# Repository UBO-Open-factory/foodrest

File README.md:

> **Attention**
> Ce projet est en cours de développement.

# FoodRest
Code pour le Projet de poubelle connectée basée sur la solution Open Source [TOCIO](https://github.com/UBO-Open-factory/TOCIO-Back-office) permettant de collecter et afficher des données.

Ce projet présente le code Arduino pour un ESP32.

# Principe de fonctionnement du programme
Principe d’enregistrement de mesures lors de l’utilisation de la poubelle connectée.

En jaune : Les interactions avec l’utilisateur.
En Rouge, ce qu'il faut encore affiner.

# Installations
## Librairies Arduino utilisées
Plusieures librairies tierces sont utilisées dans le projet, pour faciliter l'intégration elles sont toutes mises 
dans le répertoire **Librairies**. 
Il suffi donc de les prendre et de les glisser dans le répertoire Arduino/librairies 
(Sous windows : C:\Users\<user>\Documents\Arduino\libraries en remplacant <user> par votre nom d'utilisateur windows.

### SDConfigFile
La librairie **SDConfigFile** est la librairie disponible sur le [dépot Git](https://github.com/bneedhamia/sdconfigfile)

Cette librairie est également disponible dans le répertoire du projet (répertoire /Librairies/SDConfigFile ).

### WiFiClientSecure
La librairie **WiFiClientSecure** est la librairie disponible sur le [dépot Git](https://github.com/espressif/arduino-esp32/tree/master/libraries/WiFiClientSecure)

Cette librairie est également disponible dans le répertoire du projet (répertoire /Librairies/WiFiClientSecure ).

### RTC
La librairie **RTC** utilisée est celle disponible sur le [dépot Git officiel Adafruit](https://github.com/adafruit/RTClib)
[Mode d'emploi](https://learn.adafruit.com/adafruit-pcf8523-real-time-clock?view=all)

Cette librairie est également disponible dans le répertoire du projet (répertoire /Librairies/RTClib ).

### Balance (HX711)
La librairie **HX711** utilisée est celle disponible sur le [dépot GIT](https://github.com/bogde/HX711)

Cette librairie est également disponible dans le répertoire du projet (répertoire /Librairies/HX711 ).

## Dépendance des librairies utilisées
Les librairies doivent être incluses les unes par rapport au autres dans l'ordre suivant :
* globalVariable.h
  * SPI.h
* GestionErreur.h
* Config.h
  * SDCard.h
	* SDConfigFile.h
		* SD.h
	* FS.h
	* SPI.h
* Tocio.h
  * WiFiClientSecure.h
    * WiFi.h
* Balance.h
  * HX711.h
* RTC.h
  * Wire.h
  * RTClib.h
  * NTPClient.h
  * WiFiUDP.h
* IDpoubelle.h
* Functions.h
  * Wire.h

# Configuration de Arduino
## Installation des cartes ESP32 dans l'IDe Arduino
Lancez l’IDE Arduino et ouvrez les préférences depuis le menu Fichier. Sur macOS, allez dans le menu Arduino puis Préférences… Cliquez sur l’icône indiquée par la flèche rouge sur la photo ci-dessous.

Dans le champ de saisie, collez l’adresse internet suivante puis validez
```
https://dl.espressif.com/dl/package_esp32_index.json
```
> Si vous avez déjà des définitions de cartes, vous pouvez les cumuler en les les séparant par des virgules.
> Par exemple, dans mon cas j'ai : http://arduino.esp8266.com/stable/package_esp8266com_index.json,https://dl.espressif.com/dl/package_esp32_index.json

Maintenant, allez dans le menu Outils > Type de Cartes > Gestionnaire de carte.
Dans le champ de recherche, saisissez ESP32 pour trouver les nouvelles cartes à installer. Si les cartes n’apparaissent pas, vérifiez dans les préférences que l’URL est correcte. vérifiez également la connexion Internet. Cliquer sur Installer

L’installation terminée, fermez le gestionnaire de carte et ouvrez de nouveau le menu Outils > Type de Carte. 
Vous avez maintenant une nouvelle section appelée ESP32 Boards (2.7.4)

## Sélection de la carte

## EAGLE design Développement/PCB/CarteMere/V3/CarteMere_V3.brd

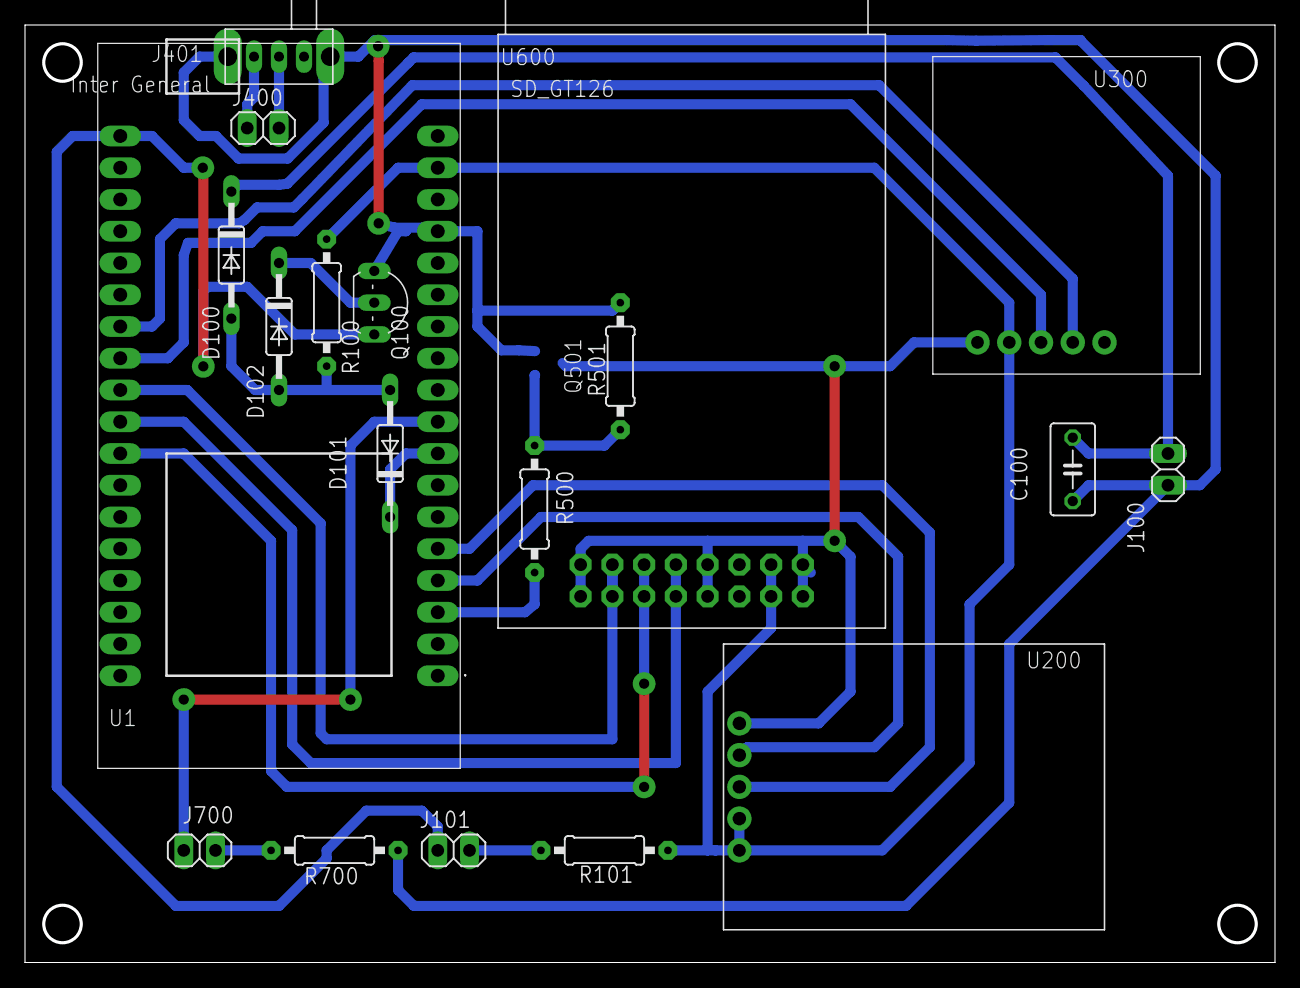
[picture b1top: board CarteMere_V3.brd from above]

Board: 2 copper layers, 99.7 x 74.7 mm, 20 parts (1 on the bottom side), 22 nets.

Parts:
C100: 10n; C050-035X075
D100, D101, D102: 1N4148; DO35-10
J100: Capteur ILS; 1X02
J101: LED_CAPOT; 1X02
J400: Inter batterie; 1X02
J401: Inter General; COMMUTATEUR_GLISSIERE_1RT_100MA
J700: LED_PESEE; 1X02
Q100: 2N5551; TO92-EBC
Q501: SI2302DS; SOT23
R100: 100k; 0207/10
R101: 470R; 0207/10
R500, R700: 100R; 0207/10
R501: 1M; 0207/10
U1: FIREBEETLE-ESP32-DFR0478; FIREBEETLE_ESP32
U200: HX711; SPARKFUN_HX711_LOAD_CELL
U300: RTC_ADA-3295; ADA3295
U600: SD_GT126

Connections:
3V3: R100.2, R101.2, U1.17, U200.VCC, U200.VDD, U300.2, U600.3V3@6, U600.3V3@9
GND: C100.2, J100.1, J401.GNDA, J401.GNDB, Q100.E, Q501.2, R501.1, R700.1, U1.15
GND_C: Q501.3, U200.GND, U300.1, U600.CS@4, U600.CS@11, U600.GND@0, U600.GND@7, U600.GND@8, U600.GND@15
GND_C_EN: R500.1, U1.3
HX711_CLK: U1.4, U200.CLK
HX711_DAT: U1.5, U200.DAT
I2C_SCL: U1.30, U300.4
I2C_SDA: U1.29, U300.3
LED_CAPOT_PLUS: J101.1, R101.1
LED_PESEE: J700.1, U1.9
MASQUE_RESET_EN: D101.C, U1.8
unnamed: Q501.1, R500.2, R501.2
unnamed: J700.2, R700.2
unnamed: D100.A, D101.A, D102.A, R100.1
unnamed: C100.1, D100.C, J100.2
unnamed: D102.C, Q100.B
unnamed: J400.2, J401.COM
unnamed: J400.1, J401.OUTA
RESET: J101.2, Q100.C, U1.36
SPI_MISO: U1.28, U600.MISO@1, U600.MISO@14
SPI_MOSI: U1.27, U600.MOSI@3, U600.MOSI@12
SPI_SCK: U1.26, U600.SCK@2, U600.SCK@13

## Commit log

2021-03-08 Librairie Arduino
2021-03-08 verssion test non_fontionnel
2021-03-08 integration lib wificlient secure
2021-03-08 suppression de variable
    !attention fonction :sendDataInHTTPSRequest(String data)
    non fonctionnel
2021-03-08 Initialisation du wifi
2021-03-08 Nettoyage du code
2021-03-09 Séparation du code en librairies
2021-03-09 Factorisation du code dans les fichiers de fonctions
2021-03-09 complément fonction + ajout fonction + commentary
    - ajout du pin maping des indicateur visuel + capteur CZL635_20
    - complement fonction CZL635_20 capteur de poid
    - complement fonction RTC en cours
    - ajout lien preference carte firebeetle esp8266
2021-03-09 complément fonction RTC "pcf8523"
2021-03-09 suppression bout de code RTC inutile + procedure de test
2021-03-09 Mise en place de la structure du main
2021-03-09 ajout lib capteur poid, nom lib "HX711"
2021-03-10 Utilisation du fichier de paramétrage pour la calibration
2021-03-10 Nettoyage de code et commentaires
2021-03-10 Suppression code innutil
2021-03-10 librairie RTC
2021-03-10 Correction erreur de typo
2021-03-10 Lecture de la configuration à partir de la (fake) carte SD
    Pour l'instant on utilise une fonction avec les paramètres écrit en dur
2021-03-10 Algorythme d'envoie des mesures.
2021-03-10 La fonction RTC doit renvoyer une string
2021-03-10 Documentation des librairies utilisées
2021-03-12 Modification de l'URL pour le BO de TOCIO
    On utilise maintenant le BO spécifique au projet Food Rest
2021-03-12 wificlient sercure non compatible firebeetle
2021-03-12 correction connection wifi version 2016
2021-03-12 space
2021-03-12 tentative de deggu
    pb au niveau de fonction -> niveau_battrie
    apres le "debug f2"
2021-03-12 Création d'un fichier de configuration type
    Ce fichier sera à mettre sur la carte SD
2021-03-12 Mise en place du calibrage usine
2021-03-12 Mise en place de la fonction de calibrage usine
2021-03-15 Formattage rapide du fichier de configuration externe
2021-03-15 Ajout de l'image de l'Algorythme
2021-03-15 Ajout de la légende du graphique
2021-03-15 Envoie de data dans le BO TOCIO
    La trame envoyée est bien reçue dans le BO. IL faut maintenant mettre de vrais données.
2021-03-16 Documentation
2021-03-16 Documentation sur l'installation de l'environnement de Développement
    Documentation faite pour Windows
2021-03-16 Configuraiton de l'IDE Arduino
2021-03-16 Mise à jour capture écran
2021-03-16 Lecture des configurations à partir de la carte SD
2021-03-16 Librairie de lecture de fichier de configuration
2021-03-17 Data sur carte SD
    Ecriture des données sur carte SD
2021-03-17 Data sur carte SD
2021-03-17 Allumage et extinction de la LED Rouge
    Mise à jour de l'algorythme pour prendre en compte l'allumage et l'extinction de la LED Rouge tout au long des mesure, envoies et sauvegarde des données.
2021-03-17 Optimisation de l'affichage des traces de debug et message erreur
2021-03-17 Clignotement LED
    La LED clignote plus ou moins rapidement en fonction de l'erreur rencontré.
2021-03-17 Formattage du code
2021-03-23 Formatage du code
2021-03-23 Initialisation de la RTC
2021-03-23 Optimisation de la gestion des message de debug
2021-03-23 Nettoyage de code
    Suppression de variable inutiles
2021-03-23 Intégration de la procédure de calibration de la balance
2021-03-23 Mise à jour des dépendance des librairies utilisées
    https://github.com/UBO-Open-factory/foodrest/projects/1#card-57529780
2021-03-24 Correction de trace lors du calibrage de la balance
2021-03-24 Mise à jour des dépendances de la RTC
2021-03-24 Déplacement des imports de librairie
2021-03-24 Externalisation des fonctions RTC
2021-03-24 Mise à jour des dépendances de librairies
2021-03-24 Suppression code mort
2021-03-24 Calibration factor de la balance
2021-03-24 Procédure d'effacement du fichier de settings
2021-03-24 Renommage du fichier principal
2021-03-24 Récupération de la sur un serveur de temps
2021-03-24 Déclaration de variables pour la batterie
2021-03-24 Documentation de l'installation des cartes NODE MCU dans l'IDE Arduino
2021-03-24 Mesure du poids réel.
2021-03-24 Simplification des variables
2021-03-24 Simulation du DeepSleep
    Affichage d'un message sur le terminal Série et clignotement très lent de la LED.
2021-03-24 Passage en DeepSleep uniquement si on est pas en mode debug.
    Le mode Debug est à mettre à true/false dans le fichier de settingsd.
2021-03-26 Test
2021-03-26 Revert "Test"
    This reverts commit 1f74ff42ec3f7e3a430da9ade52e4695863db33d.
2021-03-26 Inversion des pins de la balance
2021-03-26 Correction bug sur fichier Wifi
    correction du bug qui remplissiat à chaque boot le fichier wifi.txt
2021-03-26 Ajout deIDpoubelle.h dans des dépendances de librairies
2021-03-26 annulation de la modif wifi
2021-03-29 Saisie de l'identifiant de la poubelle lors du paramétrage usine
2021-03-29 Nettoyage du code mort
2021-03-29 Ajout du répertoire pour le projet avec un ESP32
2021-03-29 Mise à jour des liens sur les projets
2021-03-31 Installation de l'ESP32 dans l'IDE Arduino
2021-03-31 Adaptation pour la librairie wifi de l'ESP32
2021-03-31 Adaptation pour la conection à un ESP32
2021-03-31 Changement de gestionnaire de cartes ESP32
2021-03-31 Utilisation d'un ESP32
2021-03-31 Utilisation de la librairie FS
    Il faut donc avoir des chemin relatif dans les noms de fichiers
2021-03-31 Lecture du serveur de temps à l'intérieur de l'Université ou sinon un public
2021-03-31 Ecriture de l'entete du fichier CSV à la création de l'ID de la poubelle
2021-03-31 Lecture du résultat provenant du server TOCIO lors de l'envoie de données
2021-03-31 Ecriture en ajout dans les fichiers
2021-03-31 Formatage de la date et l'heure
2021-03-31 Documentation du clignotement de la LED
2021-03-31 documentation clignotement de la LED
2021-03-31 mise à jour des liens sur les images
2021-04-01 Modification du lien sur l'image
2021-04-01 Masque reset ok - deepsleep adapté à ESP32
    Masque reset ok.
    Instruction deep sleep modifiée pour s'adapter à l'ESP 32
2021-04-01 synchro usb/IDE
    Insertion d'un rappel visuel pour lancer la calibration (resynchro du port USB) de l'IDE
2021-04-01 Nouvelle procédure de tarage
    nouvelle procédure de tarage et de calibration
2021-04-01 Modification algorithme pesée
    Modification algorithme pesée
2021-04-02 Erreurs - batterie
    Gestion des erreurs OK
    Gestion batterie OK
    Affichage code erreur LED OK
2021-04-02 Amélioration tarage et pesée
    Augmentation du nb d'échantillons pour le tarage et la pesée
2021-04-05 AjoutFichierV2
    Ajout
    -Sch
    -Brd
2021-04-05 Ajout implantation et Schematic
2021-04-05 add V3
2021-04-07 Remplacement fonction formatString
2021-04-07 Envoie du poids différentiel vers TOCIO et carte SD
2021-04-12 Version initiale
2021-04-12 essai
2021-04-12 Test RTC
2021-04-12 mode deep sleep et conso
2021-04-12 amélioratio ergonomie lors du test du masque de reset
2021-04-15 Version initiale du test du capteur de poids
2021-04-15 Revert "amélioratio ergonomie lors du test du masque de reset"
    This reverts commit 19ff1e5a32dd46688be4340788a163506d01d619.
2021-04-15 Revert "Revert "amélioratio ergonomie lors du test du masque de reset""
    This reverts commit 17266f0c9c751e1c4a432e6d3d13e4b85a4944e8.
2021-04-15 Déclaration des variables
2021-04-15 Déclaration des variables globales
2021-04-15 Lecture et écriture des variables
2021-04-15 Initialisation des variables
2021-04-15 Nettoyage de code
2021-04-15 Mesure du poids brute
2021-04-15 Ecriture de la mesure brute dans le fichier CSV
2021-04-15 Suppression du retour chariot lors de la saisie du l'ID de le poubelle.
2021-04-15 Correction commentaire
2021-04-16 Changement de librairie HX711 pour les pesées avec un ESP
2021-04-16 Test capteur poids avec bibliothèque HX711-ESP
2021-04-16 Mise à jour des fichiers
2021-04-16 Utilisation de la librairie HX711 pur ESP8266
2021-04-16 Suppression du facteur de calibration initiale
2021-04-16 Renommage de fichier
2021-04-16 Changement du nombre d'échantillons fait pour une pesée
2021-04-16 Qualibration usine par défaut
    On met cette valeur à true pour que lorsqu'on met pour la première fois une carte SD dans le lecteur, la procédure de calibration usine se lance.
2021-04-16 Formatage usine :Correction de texte
2021-04-16 Extinction de la balance avant la mise en deep sleep
2021-04-16 Orthographe
2021-04-16 Tests divers (#23)
    * Version initiale
    * Test RTC
    * mode deep sleep et conso
    * amélioration ergonomie lors du test du masque de reset
    * Version initiale du test du capteur de poids
    * Déclaration des variables globales
2021-04-20 Renommage de la variable de mesure de la tare initiale
2021-04-21 Arrondi après les mesures
    Arrondi les float après les mesures et avant le formatString
2021-04-21 modif de la tolérance de vidage
    passe à 20 g pour tout les poids
2021-04-21 amelioration du calcul des pesées
2021-04-21 modifications générales
2021-04-23 Patch pour la sauvegarde de float dans un integer
    On multiplie la valeur par 100 avant la sauvegarde et on la divise par 100 à la lecture;
2021-04-23 Calcul avec des float (et non des integer)
2021-04-23 Patch convertion en float
2021-06-15 création architecture des dossier
    - ajout dossier "développement"
2021-06-15 ignore fichier DS_Store
2021-06-15 suppr DS_Store
2021-06-15 changer foodrest->foodrests
2021-06-15 Réorganisation des dossiers
2021-10-14 Version stable
    Programmée dans toutes les poubelles de la 2ème campagne de mesures
2021-10-14 ajout du cartouche de commentaire en tête du programme principal
2021-10-14 Mise a jour V1.0
    Ajout du cartouche d'en-tête (auteurs, version, date, licence)
2021-10-14 Ajout des fichiers de configuration
    Ajout dans l'arborescence des fichiers de configurations (wifi et config)
2021-10-14 Réorganisation des répertoires
